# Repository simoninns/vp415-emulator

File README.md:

# VP415 Emulator
## Project status
This is a purely experimental repo and is not for any kind of production use.

## Disclaimer
Whatever is in this repository is fiction and should not be taken seriously. All similarities with real world designs and coding was not intentional

## Author
VP415 Emulator is designed and maintained by Simon Inns.

## Software License (GPLv3)

    This is free software: you can redistribute it and/or modify
    it under the terms of the GNU General Public License as published by
    the Free Software Foundation, either version 3 of the License, or
    (at your option) any later version.

    This software is distributed in the hope that it will be useful,
    but WITHOUT ANY WARRANTY; without even the implied warranty of
    MERCHANTABILITY or FITNESS FOR A PARTICULAR PURPOSE.  See the
    GNU General Public License for more details.

    You should have received a copy of the GNU General Public License
    along with this program.  If not, see <http://www.gnu.org/licenses/>.

## Hardware License (Creative Commons BY-SA 4.0)
Please see the following link for details: https://creativecommons.org/licenses/by-sa/4.0/

You are free to:

Share - copy and redistribute the material in any medium or format
Adapt - remix, transform, and build upon the material
for any purpose, even commercially.

This license is acceptable for Free Cultural Works.

The licensor cannot revoke these freedoms as long as you follow the license terms.

Under the following terms:

Attribution - You must give appropriate credit, provide a link to the license, and indicate if changes were made. You may do so in any reasonable manner, but not in any way that suggests the licensor endorses you or your use.

ShareAlike - If you remix, transform, or build upon the material, you must distribute your contributions under the same license as the original.

No additional restrictions - You may not apply legal terms or technological measures that legally restrict others from doing anything the license permits.

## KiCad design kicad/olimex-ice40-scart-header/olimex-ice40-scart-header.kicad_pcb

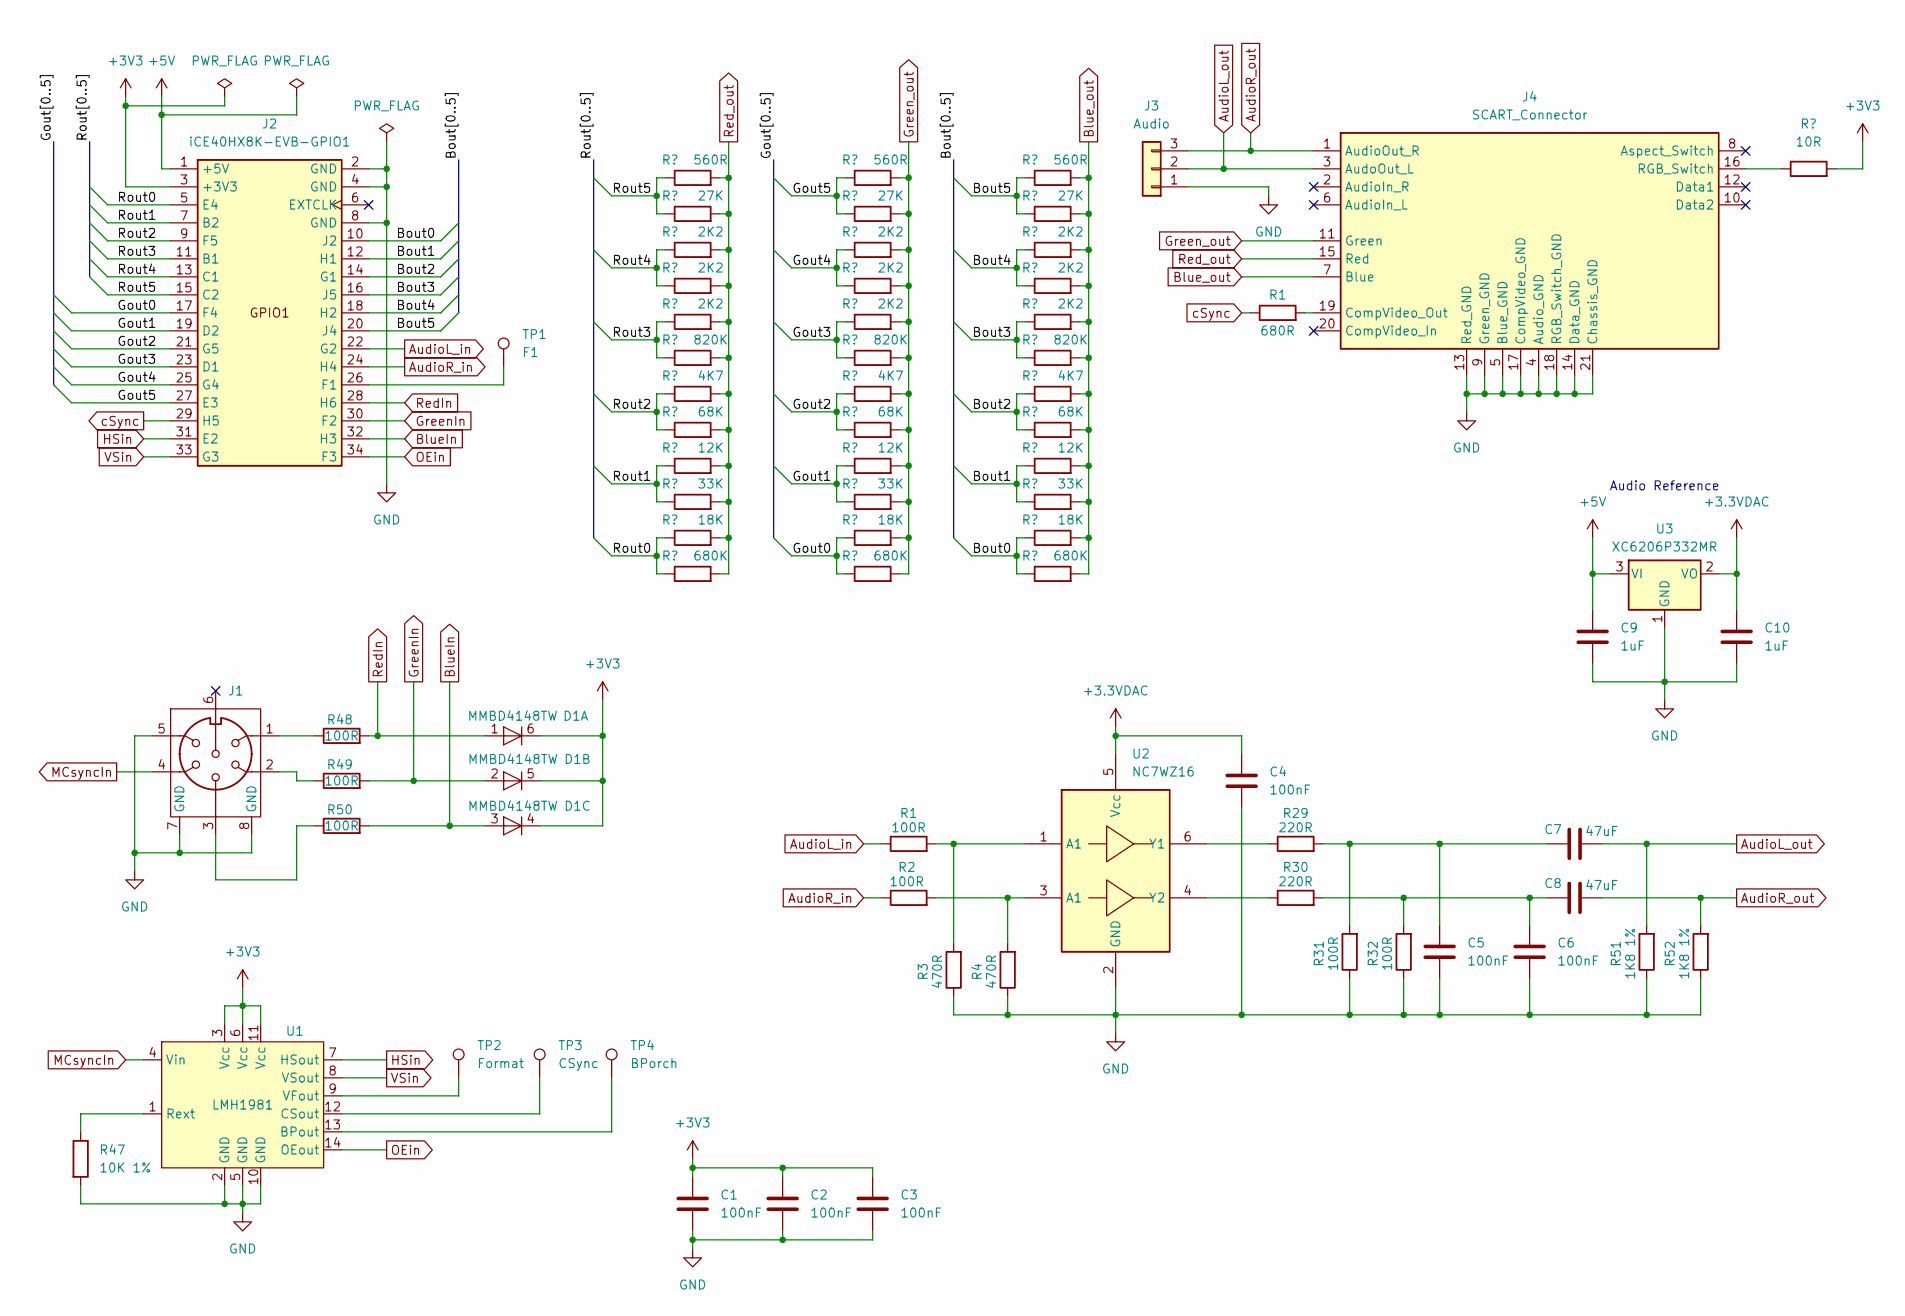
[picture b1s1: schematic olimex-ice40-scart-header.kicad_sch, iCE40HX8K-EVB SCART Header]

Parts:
C1, C2, C3, C4, C5, C6: 100nF; C_0603_1608Metric_Pad1.08x0.95mm_HandSolder
C7, C8: 47uF; C_0603_1608Metric_Pad1.08x0.95mm_HandSolder
C9, C10: 1uF; C_0603_1608Metric_Pad1.08x0.95mm_HandSolder
D1: MMBD4148TW; SOT-363_SC-70-6
J1: 6P DIN Socket RS Pro
J2: iCE40HX8K-EVB-GPIO1; IDC-Header_2x17_P2.54mm_Horizontal
J3: Audio; PinHeader_1x03_P2.54mm_Vertical
J4: SCART_Connector; HSM_C0381-21RYATB0R
R1: 680R; R_0603_1608Metric_Pad0.98x0.95mm_HandSolder
R2, R31, R32, R48, R49, R50: 100R; R_0603_1608Metric_Pad0.98x0.95mm_HandSolder
R3, R4: 470R; R_0603_1608Metric_Pad0.98x0.95mm_HandSolder
R5, R17, R33: 560R; R_0603_1608Metric_Pad0.98x0.95mm_HandSolder
R6, R18, R34: 27K; R_0603_1608Metric_Pad0.98x0.95mm_HandSolder
R7, R8, R9, R19, R20, R21, R35, R36, R37: 2K2; R_0603_1608Metric_Pad0.98x0.95mm_HandSolder
R10, R22, R38: 820K; R_0603_1608Metric_Pad0.98x0.95mm_HandSolder
R11, R23, R39: 4K7; R_0603_1608Metric_Pad0.98x0.95mm_HandSolder
R12, R24, R40: 68K; R_0603_1608Metric_Pad0.98x0.95mm_HandSolder
R13, R25, R41: 12K; R_0603_1608Metric_Pad0.98x0.95mm_HandSolder
R14, R26, R42: 33K; R_0603_1608Metric_Pad0.98x0.95mm_HandSolder
R15, R27, R43: 18K; R_0603_1608Metric_Pad0.98x0.95mm_HandSolder
R16, R28, R44: 680K; R_0603_1608Metric_Pad0.98x0.95mm_HandSolder
R29, R30: 220R; R_0603_1608Metric_Pad0.98x0.95mm_HandSolder
R46: 10R; R_0603_1608Metric_Pad0.98x0.95mm_HandSolder
R47: 10K 1%; R_0603_1608Metric_Pad0.98x0.95mm_HandSolder
R51, R52: 1K8 1%; R_0603_1608Metric_Pad0.98x0.95mm_HandSolder
TP1: F1; TestPoint_Pad_1.5x1.5mm
TP2: Format; TestPoint_Pad_1.5x1.5mm
TP3: CSync; TestPoint_Pad_1.5x1.5mm
TP4: BPorch; TestPoint_Pad_1.5x1.5mm
U1: LMH1981; TSSOP-14_4.4x5mm_P0.65mm
U2: NC7WZ16; SOT-363_SC-70-6_Handsoldering
U3: XC6206P332MR; SOT-23-3

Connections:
+3.3VDAC: C4.1, C10.1, U2.5 (Vcc), U3.2 (VO)
+3V3: C1.1, C2.1, C3.1, D1.4 (K), D1.5 (K), D1.6 (K), J2.3 (+3V3), R46.2, U1.3 (Vcc), U1.6 (Vcc), U1.11 (Vcc)
+5V: C9.1, J2.1 (+5V), U3.3 (VI)
/Bout0: J2.10 (J2), R43.1, R44.1
/Bout1: J2.12 (H1), R41.1, R42.1
/Bout2: J2.14 (G1), R39.1, R40.1
/Bout3: J2.16 (J5), R37.1, R38.1
/Bout4: J2.18 (H2), R35.1, R36.1
/Bout5: J2.20 (J4), R33.1, R34.1
/Gout0: J2.17 (F4), R27.1, R28.1
/Gout1: J2.19 (D2), R25.1, R26.1
/Gout2: J2.21 (G5), R23.1, R24.1
/Gout3: J2.23 (D1), R21.1, R22.1
/Gout4: J2.25 (G4), R19.1, R20.1
/Gout5: J2.27 (E3), R17.1, R18.1
/Rout0: J2.5 (E4), R15.1, R16.1
/Rout1: J2.7 (B2), R13.1, R14.1
/Rout2: J2.9 (F5), R11.1, R12.1
/Rout3: J2.11 (B1), R9.1, R10.1
/Rout4: J2.13 (C1), R7.1, R8.1
/Rout5: J2.15 (C2), R5.1, R6.1
AudioL_out: C7.2, J3.2, J4.3 (AudoOut_L), R51.2
AudioR_in: J2.24 (H4), R2.1
AudioR_out: C8.2, J3.3, J4.1 (AudioOut_R), R52.2
BlueIn: D1.3 (A), J2.32 (H3), R50.2
Blue_out: J4.7 (Blue), R33.2, R34.2, R35.2, R36.2, R37.2, R38.2, R39.2, R40.2, R41.2, R42.2, R43.2, R44.2
GND: C1.2, C2.2, C3.2, C4.2, C5.2, C6.2, C9.2, C10.2, J1.5, J1.7 (GND), J1.8 (GND), J2.2 (GND), J2.4 (GND), J2.8 (GND), J3.1, J4.4 (Audio_GND), J4.5 (Blue_GND), J4.9 (Green_GND), J4.13 (Red_GND), J4.14 (Data_GND), J4.17 (CompVideo_GND), J4.18 (RGB_Switch_GND), J4.21 (Chassis_GND), R3.1, R4.1, R31.1, R32.1, R47.2, R51.1, R52.1, U1.2 (GND), U1.5 (GND), U1.10 (GND), U2.2 (GND), U3.1 (GND)
GreenIn: D1.2 (A), J2.30 (F2), R49.2
Green_out: J4.11 (Green), R17.2, R18.2, R19.2, R20.2, R21.2, R22.2, R23.2, R24.2, R25.2, R26.2, R27.2, R28.2
HSin: J2.31 (E2), U1.7 (HSout)
MCsyncIn: J1.4, U1.4 (Vin)
unnamed: C5.1, C7.1, R29.2, R31.2
unnamed: C6.1, C8.1, R30.2, R32.2
unnamed: J1.1, R48.1
unnamed: J1.2, R49.1
unnamed: J1.3, R50.1
unnamed: J2.26 (F1), TP1.1
unnamed: J4.16 (RGB_Switch), R46.1
unnamed: R2.2, R4.2, U2.3 (A1)
unnamed: TP4.1, U1.13 (BPout)
unnamed: TP3.1, U1.12 (CSout)
unnamed: R47.1, U1.1 (Rext)
unnamed: TP2.1, U1.9 (VFout)
unnamed: R29.1, U2.6 (Y1)
unnamed: R30.1, U2.4 (Y2)
OEin: J2.34 (F3), U1.14 (OEout)
RedIn: D1.1 (A), J2.28 (H6), R48.2
Red_out: J4.15 (Red), R5.2, R6.2, R7.2, R8.2, R9.2, R10.2, R11.2, R12.2, R13.2, R14.2, R15.2, R16.2
VSin: J2.33 (G3), U1.8 (VSout)

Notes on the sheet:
Audio Reference

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
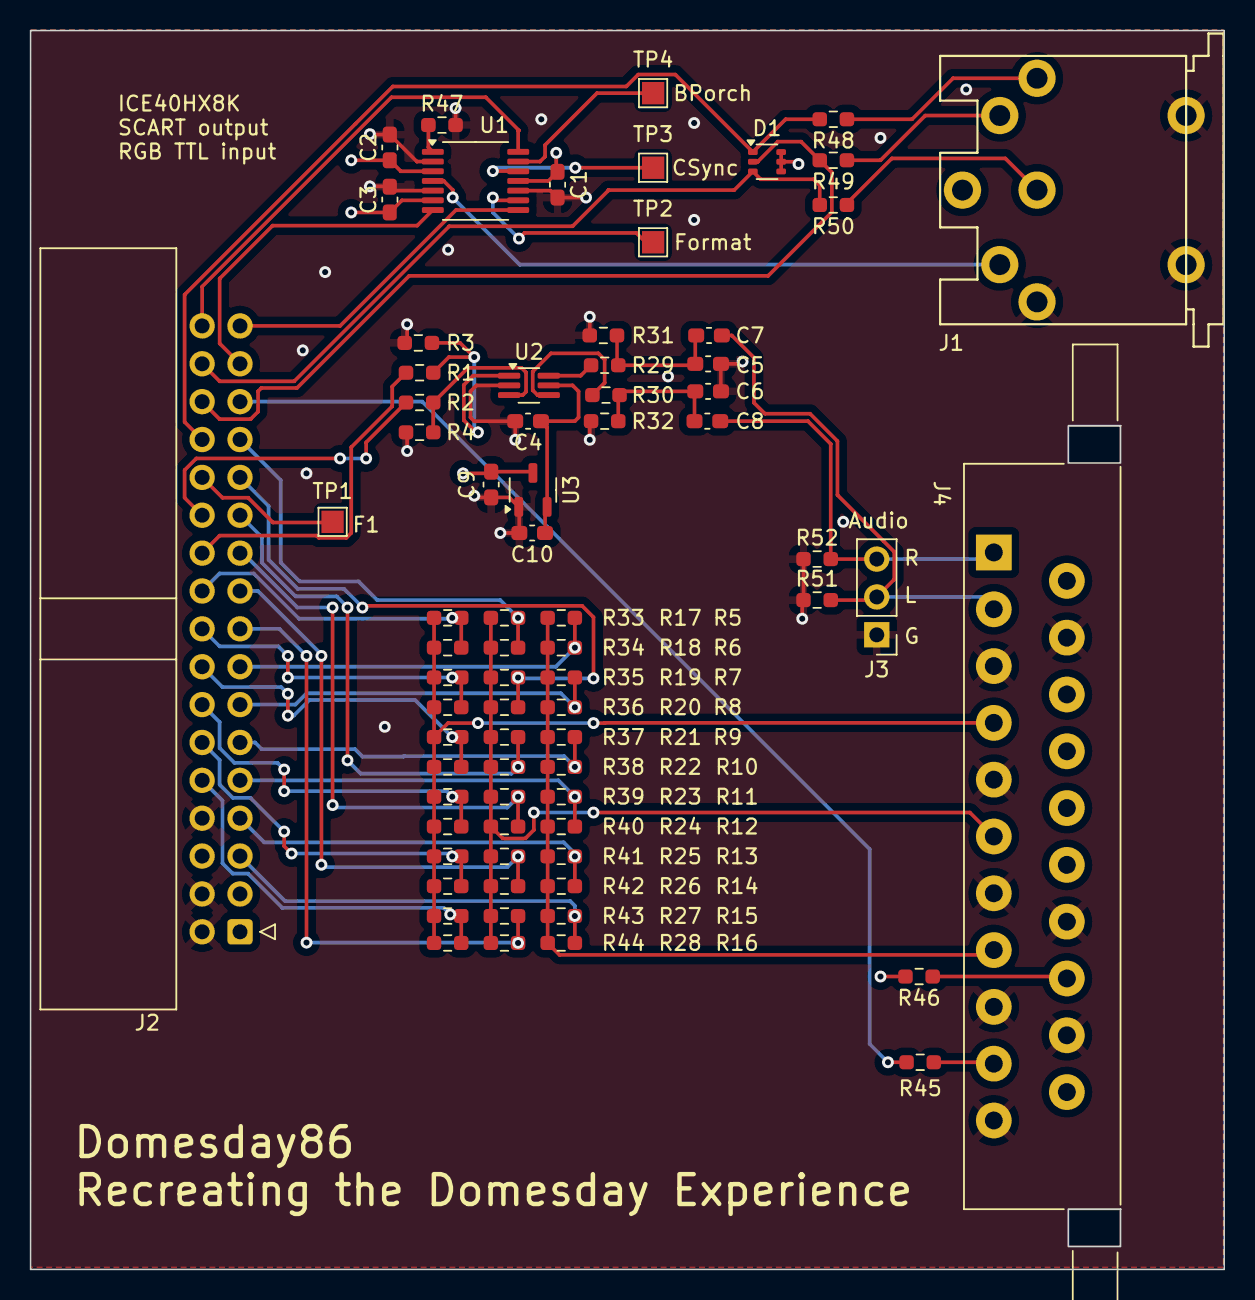
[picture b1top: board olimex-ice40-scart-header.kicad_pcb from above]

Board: 4 copper layers, 80.1 x 83.1 mm, 74 parts (0 on the bottom side), 53 nets.

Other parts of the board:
R45: 680R; R_0603_1608Metric_Pad0.98x0.95mm_HandSolder

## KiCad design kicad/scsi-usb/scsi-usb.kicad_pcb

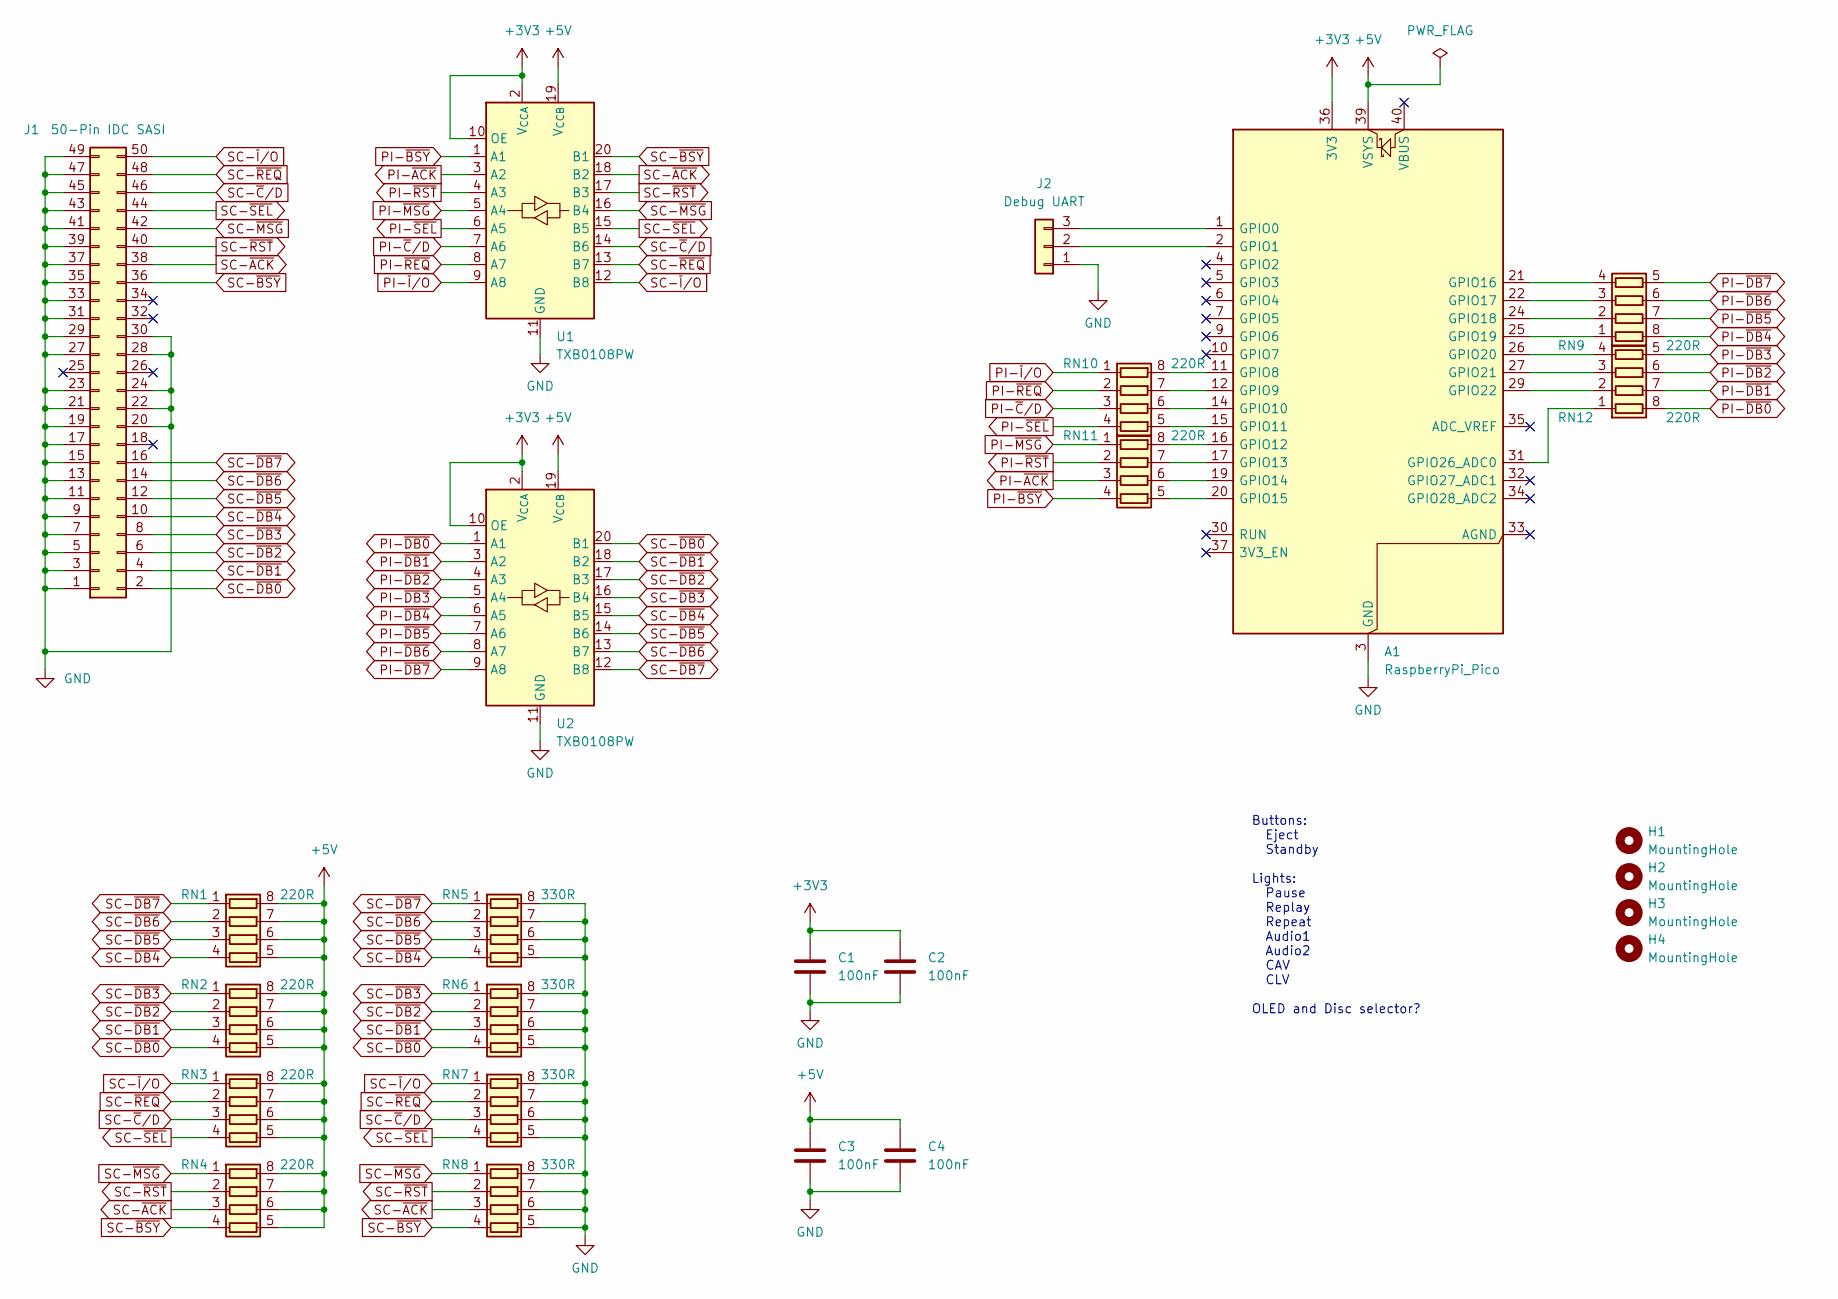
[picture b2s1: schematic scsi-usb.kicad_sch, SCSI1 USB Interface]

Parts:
A1: RaspberryPi_Pico; RaspberryPi_Pico_Common
C1, C2, C3, C4: 100nF; C_0805_2012Metric
H1, H2, H3, H4: MountingHole; MountingHole_3.2mm_M3
J1: 50-Pin IDC SASI; IDC-Header_2x25_P2.54mm_Latch_Horizontal
J2: Debug UART; PinHeader_1x03_P2.54mm_Vertical
RN1, RN2, RN3, RN4, RN9, RN10, RN11, RN12: 220R; R_Array_Convex_4x1206
RN5, RN6, RN7, RN8: 330R; R_Array_Convex_4x1206
U1, U2: TXB0108PW; TSSOP-20_4.4x6.5mm_P0.65mm

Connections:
+3V3: A1.36 (3V3), C1.1, C2.1, U1.2 (V_{CCA}), U1.10 (OE), U2.2 (V_{CCA}), U2.10 (OE)
+5V: A1.39 (VSYS), C3.1, C4.1, RN1.5 (R4.2), RN1.6 (R3.2), RN1.7 (R2.2), RN1.8 (R1.2), RN2.5 (R4.2), RN2.6 (R3.2), RN2.7 (R2.2), RN2.8 (R1.2), RN3.5 (R4.2), RN3.6 (R3.2), RN3.7 (R2.2), RN3.8 (R1.2), RN4.5 (R4.2), RN4.6 (R3.2), RN4.7 (R2.2), RN4.8 (R1.2), U1.19 (V_{CCB}), U2.19 (V_{CCB})
GND: A1.3 (GND), A1.8 (GND), A1.13 (GND), A1.18 (GND), A1.23 (GND), A1.28 (GND), A1.38 (GND), C1.2, C2.2, C3.2, C4.2, J1.1, J1.3, J1.5, J1.7, J1.9, J1.11, J1.13, J1.15, J1.17, J1.19, J1.20, J1.21, J1.22, J1.23, J1.24, J1.27, J1.28, J1.29, J1.30, J1.31, J1.33, J1.35, J1.37, J1.39, J1.41, J1.43, J1.45, J1.47, J1.49, J2.1, RN5.5 (R4.2), RN5.6 (R3.2), RN5.7 (R2.2), RN5.8 (R1.2), RN6.5 (R4.2), RN6.6 (R3.2), RN6.7 (R2.2), RN6.8 (R1.2), RN7.5 (R4.2), RN7.6 (R3.2), RN7.7 (R2.2), RN7.8 (R1.2), RN8.5 (R4.2), RN8.6 (R3.2), RN8.7 (R2.2), RN8.8 (R1.2), U1.11 (GND), U2.11 (GND)
unnamed: A1.1 (GPIO0), J2.3
unnamed: A1.2 (GPIO1), J2.2
unnamed: A1.11 (GPIO8), RN10.8 (R1.2)
unnamed: A1.12 (GPIO9), RN10.7 (R2.2)
unnamed: A1.14 (GPIO10), RN10.6 (R3.2)
unnamed: A1.15 (GPIO11), RN10.5 (R4.2)
unnamed: A1.16 (GPIO12), RN11.8 (R1.2)
unnamed: A1.17 (GPIO13), RN11.7 (R2.2)
unnamed: A1.19 (GPIO14), RN11.6 (R3.2)
unnamed: A1.20 (GPIO15), RN11.5 (R4.2)
unnamed: A1.21 (GPIO16), RN9.4 (R4.1)
unnamed: A1.22 (GPIO17), RN9.3 (R3.1)
unnamed: A1.24 (GPIO18), RN9.2 (R2.1)
unnamed: A1.25 (GPIO19), RN9.1 (R1.1)
unnamed: A1.26 (GPIO20), RN12.4 (R4.1)
unnamed: A1.27 (GPIO21), RN12.3 (R3.1)
unnamed: A1.29 (GPIO22), RN12.2 (R2.1)
unnamed: A1.31 (GPIO26_ADC0), RN12.1 (R1.1)
PI-~ACK: RN11.3 (R3.1), U1.3 (A2)
PI-~BSY: RN11.4 (R4.1), U1.1 (A1)
PI-~C/D: RN10.3 (R3.1), U1.7 (A6)
PI-~DB0: RN12.8 (R1.2), U2.1 (A1)
PI-~DB1: RN12.7 (R2.2), U2.3 (A2)
PI-~DB2: RN12.6 (R3.2), U2.4 (A3)
PI-~DB3: RN12.5 (R4.2), U2.5 (A4)
PI-~DB4: RN9.8 (R1.2), U2.6 (A5)
PI-~DB5: RN9.7 (R2.2), U2.7 (A6)
PI-~DB6: RN9.6 (R3.2), U2.8 (A7)
PI-~DB7: RN9.5 (R4.2), U2.9 (A8)
PI-~I/O: RN10.1 (R1.1), U1.9 (A8)
PI-~MSG: RN11.1 (R1.1), U1.5 (A4)
PI-~REQ: RN10.2 (R2.1), U1.8 (A7)
PI-~RST: RN11.2 (R2.1), U1.4 (A3)
PI-~SEL: RN10.4 (R4.1), U1.6 (A5)
SC-~ACK: J1.38, RN4.3 (R3.1), RN8.3 (R3.1), U1.18 (B2)
SC-~BSY: J1.36, RN4.4 (R4.1), RN8.4 (R4.1), U1.20 (B1)
SC-~C/D: J1.46, RN3.3 (R3.1), RN7.3 (R3.1), U1.14 (B6)
SC-~DB0: J1.2, RN2.4 (R4.1), RN6.4 (R4.1), U2.20 (B1)
SC-~DB1: J1.4, RN2.3 (R3.1), RN6.3 (R3.1), U2.18 (B2)
SC-~DB2: J1.6, RN2.2 (R2.1), RN6.2 (R2.1), U2.17 (B3)
SC-~DB3: J1.8, RN2.1 (R1.1), RN6.1 (R1.1), U2.16 (B4)
SC-~DB4: J1.10, RN1.4 (R4.1), RN5.4 (R4.1), U2.15 (B5)
SC-~DB5: J1.12, RN1.3 (R3.1), RN5.3 (R3.1), U2.14 (B6)
SC-~DB6: J1.14, RN1.2 (R2.1), RN5.2 (R2.1), U2.13 (B7)
SC-~DB7: J1.16, RN1.1 (R1.1), RN5.1 (R1.1), U2.12 (B8)
SC-~I/O: J1.50, RN3.1 (R1.1), RN7.1 (R1.1), U1.12 (B8)
SC-~MSG: J1.42, RN4.1 (R1.1), RN8.1 (R1.1), U1.16 (B4)
SC-~REQ: J1.48, RN3.2 (R2.1), RN7.2 (R2.1), U1.13 (B7)
SC-~RST: J1.40, RN4.2 (R2.1), RN8.2 (R2.1), U1.17 (B3)
SC-~SEL: J1.44, RN3.4 (R4.1), RN7.4 (R4.1), U1.15 (B5)

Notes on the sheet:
Buttons: Eject Standby Lights: Pause Replay Repeat Audio1 Audio2 CAV CLV OLED and Disc selector?

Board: 2 copper layers, 25 parts (0 on the bottom side), 53 nets, no tracks yet.

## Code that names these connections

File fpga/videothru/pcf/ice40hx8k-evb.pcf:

# VP415-Emulator FPGA
# Based on the Olimex iCE40HX8K-EVB board

## 100MHz System clock
set_io -nowarn clock100Mhz J3

## Buttons
set_io -nowarn buttons[0] K11
set_io -nowarn buttons[1] P13

## LEDs
set_io -nowarn leds[0] M12
set_io -nowarn leds[1] R16

## On-board SRAM
set_io -nowarn SRAM0_nCS T6
set_io -nowarn SRAM0_nOE L9
set_io -nowarn SRAM0_nWE T7
set_io -nowarn SRAM0_A[0] N6
set_io -nowarn SRAM0_A[1] T1
set_io -nowarn SRAM0_A[2] P4
set_io -nowarn SRAM0_A[3] R2
set_io -nowarn SRAM0_A[4] N5
set_io -nowarn SRAM0_A[5] T2
set_io -nowarn SRAM0_A[6] P5
set_io -nowarn SRAM0_A[7] R3
set_io -nowarn SRAM0_A[8] R5
set_io -nowarn SRAM0_A[9] T3
set_io -nowarn SRAM0_A[10] R4
set_io -nowarn SRAM0_A[11] M7
set_io -nowarn SRAM0_A[12] N7
set_io -nowarn SRAM0_A[13] P6
set_io -nowarn SRAM0_A[14] M8
set_io -nowarn SRAM0_A[15] T5
set_io -nowarn SRAM0_A[16] R6
set_io -nowarn SRAM0_A[17] P8
set_io -nowarn SRAM0_D[0] T8
set_io -nowarn SRAM0_D[1] P7
set_io -nowarn SRAM0_D[2] N9
set_io -nowarn SRAM0_D[3] T9
set_io -nowarn SRAM0_D[4] M9
set_io -nowarn SRAM0_D[5] R9
set_io -nowarn SRAM0_D[6] K9
set_io -nowarn SRAM0_D[7] P9
set_io -nowarn SRAM0_D[8] R10
set_io -nowarn SRAM0_D[9] L10
set_io -nowarn SRAM0_D[10] P10
set_io -nowarn SRAM0_D[11] N10
set_io -nowarn SRAM0_D[12] T10
set_io -nowarn SRAM0_D[13] T11
set_io -nowarn SRAM0_D[14] T15
set_io -nowarn SRAM0_D[15] T14

## GPIO1 (34 pin right-angle IDC)
## SCART RGB666 Dev Adaptor with RGB 3-bit input
set_io -nowarn red_scartOut[0] E4
set_io -nowarn red_scartOut[1] B2
set_io -nowarn red_scartOut[2] F5
set_io -nowarn red_scartOut[3] B1
set_io -nowarn red_scartOut[4] C1
set_io -nowarn red_scartOut[5] C2

set_io -nowarn green_scartOut[0] F4
set_io -nowarn green_scartOut[1] D2
set_io -nowarn green_scartOut[2] G5
set_io -nowarn green_scartOut[3] D1
set_io -nowarn green_scartOut[4] G4
set_io -nowarn green_scartOut[5] E3

set_io -nowarn blue_scartOut[0] J2
set_io -nowarn blue_scartOut[1] H1
set_io -nowarn blue_scartOut[2] G1
set_io -nowarn blue_scartOut[3] J5
set_io -nowarn blue_scartOut[4] H2
set_io -nowarn blue_scartOut[5] J4

set_io -nowarn cSyncScart H5

set_io -nowarn redIn H6
set_io -nowarn greenIn F2
set_io -nowarn blueIn H3
set_io -nowarn cSyncIn F3

set_io -nowarn gpio1_22 G2
set_io -nowarn gpio1_24 H4
set_io -nowarn gpio1_26 F1
set_io -nowarn gpio1_31 E2
set_io -nowarn gpio1_33 G3

## EXT1 External 16M SRAM board (1)
# set_io -nowarn SRAMa_D[15] C14
# set_io -nowarn SRAMa_D[14] B15
# set_io -nowarn SRAMa_D[0] B7
# set_io -nowarn SRAMa_D[13] D13
# set_io -nowarn SRAMa_D[1] C7
# set_io -nowarn SRAMa_D[12] B14
# set_io -nowarn SRAMa_D[2] A7
# set_io -nowarn SRAMa_D[11] C12
# set_io -nowarn SRAMa_D[3] B8
# set_io -nowarn SRAMa_D[10] E11
# set_io -nowarn SRAMa_D[4] D8
# set_io -nowarn SRAMa_D[9] C13
# set_io -nowarn SRAMa_D[5] B9
# set_io -nowarn SRAMa_D[8] A16
# set_io -nowarn SRAMa_D[6] F7
# set_io -nowarn SRAMa_LDQM A15
# set_io -nowarn SRAMa_D[7] C8
# set_io -nowarn SRAMa_nWE B13
# set_io -nowarn SRAMa_nRAS F9
# set_io -nowarn SRAMa_nCAS E10
# set_io -nowarn SRAMa_CKE A9
# set_io -nowarn SRAM_A[9] C11
# set_io -nowarn SRAM_A[11] D9
# set_io -nowarn SRAM_A[8] D11
# set_io -nowarn SRAM_A[10] E9
# set_io -nowarn SRAM_A[7] B12
# set_io -nowarn SRAM_A[0] C9
# set_io -nowarn SRAM_A[6] B10
# set_io -nowarn SRAM_A[1] D10
# set_io -nowarn SRAM_A[5] B11
# set_io -nowarn SRAM_A[2] A11
# set_io -nowarn SRAM_A[4] C10
# set_io -nowarn SRAM_A[3] A10

## EXT2 External 16M SRAM board (2)
# set_io -nowarn SRAMb_D[15] B6
# set_io -nowarn SRAMb_D[14] C6
# set_io -nowarn SRAMb_D[0] J10
# set_io -nowarn SRAMb_D[13] D7
# set_io -nowarn SRAMb_D[1] M16
# set_io -nowarn SRAMb_D[12] A6
# set_io -nowarn SRAMb_D[2] K12
# set_io -nowarn SRAMb_D[11] D6
# set_io -nowarn SRAMb_D[3] L14
# set_io -nowarn SRAMb_D[10] A5
# set_io -nowarn SRAMb_D[4] L13
# set_io -nowarn SRAMb_D[9] B5
# set_io -nowarn SRAMb_D[5] N16
# set_io -nowarn SRAMb_D[8] E6
# set_io -nowarn SRAMb_D[6] L12
# set_io -nowarn SRAMb_D[7] M14
# set_io -nowarn SRAMb_LDQM M13
# set_io -nowarn SRAM_CLK D5
# set_io -nowarn SRAMa_nCS P16
# set_io -nowarn SRAMa_UDQM A1
# set_io -nowarn SRAMb_UDQM P15
# set_io -nowarn SRAMb_nWE C5
# set_io -nowarn SRAMb_nRAS P14
# set_io -nowarn SRAMb_nCAS C4
# set_io -nowarn SRAMb_nCS R15
# set_io -nowarn SRAMb_CKE B3

## EXT3 40-pin header to Raspberry Pi GPIO header
set_io -nowarn pi_gpio[2]  M15
set_io -nowarn pi_gpio[3]  J11
set_io -nowarn pi_gpio[4]  E14
set_io -nowarn pi_gpio[14] L16
set_io -nowarn pi_gpio[15] F11
set_io -nowarn pi_gpio[17] K13
set_io -nowarn pi_gpio[18] D15
set_io -nowarn pi_gpio[27] K14
set_io -nowarn pi_gpio[22] F12
set_io -nowarn pi_gpio[23] J15
set_io -nowarn pi_gpio[24] F14
set_io -nowarn pi_gpio[10] K15
set_io -nowarn pi_gpio[9]  G12
set_io -nowarn pi_gpio[25] K16
set_io -nowarn pi_gpio[11] D16
set_io -nowarn pi_gpio[8]  J14
set_io -nowarn pi_gpio[7]  G13
set_io -nowarn pi_gpio[0]  J12
set_io -nowarn pi_gpio[1]  E16
set_io -nowarn pi_gpio[5]  J13
set_io -nowarn pi_gpio[6]  G14
set_io -nowarn pi_gpio[12] J16
set_io -nowarn pi_gpio[13] F15
set_io -nowarn pi_gpio[19] H13
set_io -nowarn pi_gpio[16] G11
set_io -nowarn pi_gpio[26] H11
set_io -nowarn pi_gpio[20] F16
set_io -nowarn pi_gpio[21] H16

## EXT4 - PicoScope 16-bit Data analysis connector
set_io -nowarn picoScope[0] N4
set_io -nowarn picoScope[1] M5
set_io -nowarn picoScope[2] P2
set_io -nowarn picoScope[3] P1
set_io -nowarn picoScope[4] N3
set_io -nowarn picoScope[5] R1
set_io -nowarn picoScope[6] M4
set_io -nowarn picoScope[7] L5
set_io -nowarn picoScope[8] M3
set_io -nowarn picoScope[9] N2
set_io -nowarn picoScope[10] L7
set_io -nowarn picoScope[11] K5
set_io -nowarn picoScope[12] L3
set_io -nowarn picoScope[13] M6
set_io -nowarn picoScope[14] M2
set_io -nowarn picoScope[15] L6

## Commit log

2025-03-16 Pushing project files to github
2025-03-16 Added pico footprint kicad submodule to library
2025-03-16 Added build environment for raspberry pico sasi2usb
2025-03-16 Basic pico project now compiling and working on the Pico2
2025-03-17 Basic low-level USB handler integrated
2025-03-19 Added libusb to the basic vp415-host app
2025-03-22 Added basic picoscsi code and clanged it into shape. Added build environment.
2025-03-22 Added basic serial port handing to the Qt GUI app
2025-03-23 Added some basic low-level communciation between the Pico and the Pi5
2025-03-23 Added gitignore
2025-03-24 Added basic commands from pico to host to get to bus free state
2025-03-27 Working hsync separator code
2025-03-27 Make the beebthru code use the Pi's pixel clock * 6
2025-03-28 Changed RGB input stage for better noise performance and included a sync regeneration circuit feeding the FPGA
2025-03-28 Added csync passthru to FPGA for dev purposes
2025-03-29 Changed RGB input design again
2025-03-29 Added hsync recovery
2025-03-29 Both vertical and horizonal sync signals are regenerated
2025-03-29 Finished the sync regenerator (I hope!) - tidied up the code and made it more modular
2025-03-29 Added a csync generator
2025-03-29 Added video thru from the AIV to the SCART output and tested image quality (sync'd to Pi Pixel clock)
2025-03-29 Minor fix
2025-03-30 Added basis of new FPGA code - not working yet
2025-03-30 Fixed pixel tracking
2025-03-30 Added video mixer to test genlocking to the AIV
2025-03-30 Fixed some of the .v headers with correct information
2025-04-01 Added basic framebuffer test code project
2025-04-01 Added framebuffer code - doesn't work yet though
2025-04-01 vidmix is basically working, only the genlock is wobbling for some reason
2025-04-02 Refactor to handle RGB as a single register
2025-04-02 Clean up of FPGA code
2025-04-04 Yet another nearly working framebuffer design... this one is almost stable though :)
2025-04-04 Stable testcard through the framebuffer
2025-04-05 Added grid pattern to RGB111 test card
2025-04-05 Added start of frame flag to the pi video tracking
2025-04-05 Moved Pi start of frame signal generation to the pi pixel tracking module where it should be
2025-04-07 Bug fixes to FPGA code to get the AIV tracking back working (sort of)
2025-04-07 Working framebuffer, but AIV sampling is still out
2025-04-07 More minor fixes
2025-04-07 Fix to make it compile again
2025-04-07 Minor fixes to clean up debug
2025-04-08 Improment to dot clock phase alignment
2025-04-09 Added new test project aivin
2025-04-10 New aivin test application added to get the input correct from the AIV - not working yet

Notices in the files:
kicad/olimex-ice40-scart-header/olimex-ice40-scart-header.kicad_sch:
(c) 2023 Simon Inns
License: Attribution-ShareAlike 4.0 International (CC BY-SA 4.0)
kicad/scsi-usb/scsi-usb.kicad_sch:
(c) 2025 Simon Inns
